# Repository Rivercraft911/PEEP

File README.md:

# PEEP
The World's smallest remote-controlled keystroke injection device...
A 12.06 × 8 mm infrared-controlled USB keyboard.

<!-- Add a demo thumbnail and video link here. -->

## Hardware

- Four-layer, 0.8 mm PCB with a direct USB-A edge connection
- STM32F042G6 Cortex-M0 with crystal-less USB Full Speed
- VEMD10940F photodiode and VSOP38338 38 kHz IR receiver
- Factory USB DFU bootloader; bridge BOOT0 to 3.3 V for recovery

## Software

An IR burst starts the stored macro. PEEP sends standard USB keyboard reports, ignores IR while the macro runs, then re-arms after 250 ms of idle receiver time. Plugging it in does not start the demo.

- [Firmware, build, and flashing instructions](software/firmware/README.md)
- [XIAO ESP32-C6 Wi-Fi / IR remote](software/firmware/esp32-trigger/README.md)
- [KiCad project](PCB/peep/peep.kicad_pro) and [PCB setup](PCB/README.md)
- [BOM and production files](PCB/peep/production/)

There is no Windows companion or packet-upload protocol yet.

The firmware builds and passes native tests.

Use PEEP only on systems you own or have permission to test.

[MIT license](LICENSE). Dependencies retain their own licenses.

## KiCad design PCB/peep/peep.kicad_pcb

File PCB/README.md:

# PCB projects

Open [peep/peep.kicad_pro](peep/peep.kicad_pro) in KiCad 10. The BOM, placement files, and Gerbers are in [peep/production/](peep/production/).

Custom symbols, footprints, and 3D models come from `RiversKicadLibrary` through the `RIVERS_DIR` KiCad path variable.

The [ESP32-C6 remote](../software/firmware/esp32-trigger/README.md) uses off-the-shelf boards; there is no remote PCB yet.

## On the bench

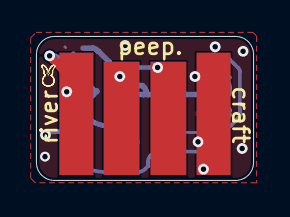
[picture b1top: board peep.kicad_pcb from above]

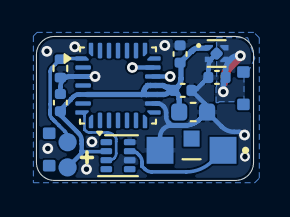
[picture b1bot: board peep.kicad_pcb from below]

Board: 4 copper layers, 12.1 x 8.0 mm, 15 parts (14 on the bottom side), 8 nets.

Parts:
C2, C3: 1uF; C_0402_1005Metric
C5, C7: 100nF; C_0402_1005Metric
C6: 4.7uF; C_0603_1608Metric
D1: VEMD10940F
J1: USB_A; PCB_USBA
R1: 10k; R_0402_1005Metric
R2, R3: R_US; Spacer_0805_SideMount_RC0805JR-070RL
TP1, TP2: TestPoint; TestPoint-1.0mm
U1: STM32F042G6Ux; ST_UFQFPN28_4x4mm_P0.5mm
U2: TPS7A0233DQNR; Texas_X2SON-4_1x1mm_P0.65mm
U3: VSOP38338

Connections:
+3V3: C3.2, C5.2, C6.2, C7.2, TP2.1 (1_1), U1.5 (VDDA), U1.17 (VDD), U1.18 (VDDIO2), U2.1 (OUT), U3.2 (VS)
+5V: C2.1, J1.1 (VBUS), U2.3 (EN), U2.4 (IN)
/BOOT0: R1.2, TP1.1 (1_1), U1.1 (PB8)
/OptoOut: U1.7 (PA1), U3.3 (~OUT)
/USB_D+: J1.3 (D+), U1.20 (PA10/PA12)
/USB_D-: J1.2 (D-), U1.19 (PA9/PA11)
GND: C2.2, C3.1, C5.1, C6.1, C7.1, D1.A, J1.4 (GND), R1.1, U1.3 (PF1), U1.16 (VSSA), U2.2 (GND), U2.5 (EP), U3.6 (GND), U3.8 (GND)
unnamed: D1.C, U3.7 (IN)

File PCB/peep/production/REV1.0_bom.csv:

Designator,Footprint,Quantity,Value,LCSC Part #
"C2, C3",0402,2,1uF,
"C5, C7",0402,2,100nF,
C6,0603,1,4.7uF,
D1,VEMD10940F,1,VEMD10940F,VEMD10940F
J1,PCB_USBA,1,USB_A,
R1,0402,1,10k,
"R2, R3",Spacer_0805_SideMount_RC0805JR-070RL,2,R_US,C96345
"TP1, TP2",TestPoint-1.0mm,2,TestPoint,
U1,QFN-28_4x4mm_P0.5mm,1,STM32F042G6Ux,
U2,Texas_X2SON-4_1x1mm_P0.65mm,1,TPS7A0233DQNR,TPS7A0233DQNR
U3,VSOP38338,1,VSOP38338,VSOP38338
